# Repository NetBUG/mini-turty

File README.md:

# mini-turty

ROS package for the Mini-Turty robot.

Original product website: https://www.rhoeby.com/product/mini-turty
    
The Mini-Turty Robot from Rhoeby Dynamics represents a new level of value and functionality in a ROS navigation-capable robot. Designed with the lowest cost and complete user serviceability in mind, this robot is providing greatly improved access to advanced robotics navigation and much more!

## Hardware
The repository contains a [sample platform](mini_turty3/hw/lasercut) designed to be made with laser cutting. 
The base is cut out of 3mm birch plywood with principal strength direction oriented transversely (i.e. robot does not bend between the wheels).
Any other elements are cut out of 3 or 4mm acrylic sheet of any color. Motor holders are not optimal and will be improved soon to provide active suspension.
Unfortunately, the front navigation module (can be seen on sheets as a rectangle of 120x85 mm) was made long ago and design was lost. It contains:
 - Raspberry Pi 3 with heatsink, mounted on 4xM2 screws on the bottom sheet;
 - Neato xv11 lidar, mounted on upper sheet (which is elevated with 30mm M3 screws and pipe-like stands)
 - Raspberry Pi 3 extension made on a prototyping board with PLS connectors, providing connections to
  * lidar through on-board UART (serial kernel logging was disabled)
  * lidar motor power through a low-power SOT23 MOSFET
  * stepper driver outputs
  * I2C connector for  sensors (used for IMU)
  * 4xGPIO pins

The following external components have been used and fit on the base:
 - [18650-sized battery holder](https://www.thingiverse.com/thing:456900)
 - [LV8729 drivers](https://www.aliexpress.com/item/32808950520.html)
 - 2xNEMA17 stepper motors with Makeblocks wheels and wheel hubs
 - A [ball stand](https://pandao.ru/product/233c3d45-5e80-4f82-84e4-e2d594d67a44)

The following components have been fit on the upper board
 - A stepdown module using XL6009 chip
 - An [IMU](https://amperka.ru/product/troyka-imu-10-dof)
 - An IR receiver
 - [Power controller board](mini_turty3/hw/controller)

Drawings use the following coloring convention:
 - black means the lines that have to be cut
 - red means lines denoting mounted parts dimensions and should be omitted when cutting (originally it was used as pale dashed line)
 - yellow originally denoted contours filled with yellow and was used in engraving mode to provide submerged areas to hide PCBs or screen frame

## Things You Can Do With Your Mini-Turty Robot

There are many things you can do with your Mini-Turty robot, including:

- Basics: ROS learning
- Teleop: robot remote control
- Map Building: make maps of your home or office for the robot to use
- Navigation: the robot moves autonomously around your home or office
- Tele-Viewing: see what your robot sees, even from another room*
- Frontier Exploration: the robot autonomously explores unknown terrain*
- Computer Vision: Mini-Turty recognizes objects in its environment*

*Coming soon, to a robot near you!

Available in kit form*, or fully assembled and ready to go. Either way, Mini-Turty provides endless hours of educational fun and represents the ideal platform for learning the Robot Operating System.

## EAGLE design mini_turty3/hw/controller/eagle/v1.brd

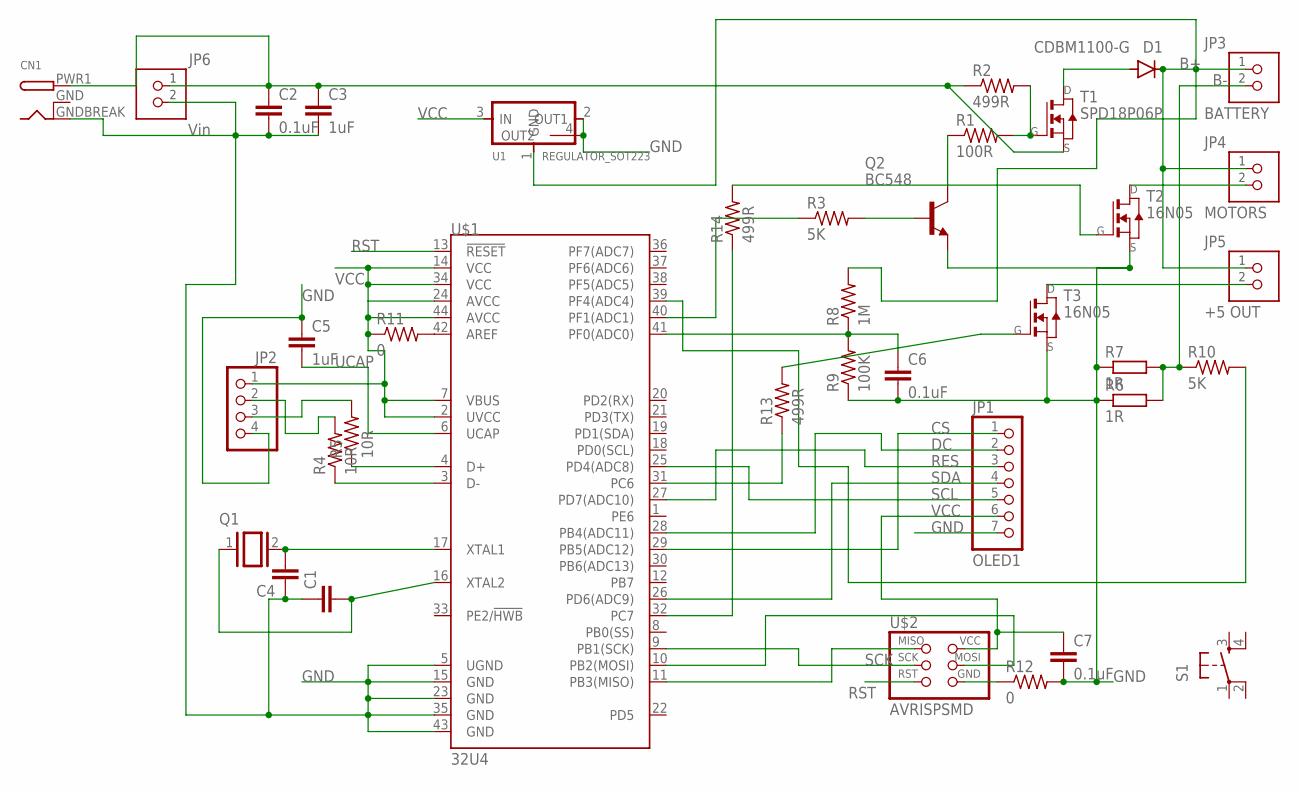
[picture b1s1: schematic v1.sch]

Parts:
C1, C4: C-EUC1206; C1206
C2, C6, C7: 0.1uF; C1206
C3, C5: 1uF; C1206
CN1: DCBARRELSMT; DCJACK_2MM_SMT
D1: CDBM1100-G; MINI-SMA
JP1: OLED1; 1X07
JP2: PINHD-1X4; 1X04
JP3: BATTERY; ED555DS-2DS
JP4: MOTORS; ED555DS-2DS
JP5: +5 OUT; ED555DS-2DS
JP6: Vin; ED555DS-2DS
Q1: XTAL/S; QS
Q2: BC548; TO92-EBC
R1: 100R; M1206
R2, R13, R14: 499R; M1206
R3, R10: 5K; M1206
R4, R5: 10R; M1206
R6, R7: 1R; R6332W
R8: 1M; M1206
R9: 100K; M1206
R11, R12: 0; M1206
S1: 6MM_SWITCH6MM_SWITCH; 6MM_SWITCH
T1: SPD18P06P; TO252
T2, T3: 16N05; TO252
U1: REGULATOR_SOT223; SOT223
U$1: 32U4; TQFP44
U$2: AVRISPSMD; 2X03SMD

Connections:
B+: D1.KATHODE, JP3.1, JP4.1, JP5.1, R8.2, U1.1 (GND)
B-: JP3.2, R6.2, R7.2, R10.1
CS: JP1.1, U$1.29 (PB5(ADC12))
DC: JP1.2, U$1.28 (PB4(ADC11))
GND: C1.1, C2.2, C3.2, C4.1, C5.1, C6.2, C7.2, CN1.GNDBREAK (GND), JP1.7, JP2.4, JP6.2, Q2.E, R6.1, R7.1, R9.1, R12.2, T2.2 (S), T3.2 (S), U1.2 (OUT1), U1.4 (OUT2), U$1.5 (UGND), U$1.15 (GND), U$1.23 (GND), U$1.35 (GND), U$1.43 (GND)
GNDBREAK: CN1.GND (GNDBREAK)
MISO: U$1.11 (PB3(MISO)), U$2.1 (MISO)
MOSI: U$1.10 (PB2(MOSI)), U$2.4 (MOSI)
unnamed: C4.2, Q1.2, U$1.17 (XTAL1)
unnamed: R11.2, U$1.42 (AREF)
unnamed: R3.1, U$1.40 (PF1(ADC1))
unnamed: R12.1, U$2.6 (GND)
unnamed: C1.2, Q1.1, U$1.16 (XTAL2)
unnamed: JP5.2, T3.3 (D)
unnamed: JP4.2, T2.3 (D)
unnamed: R14.1, U$1.32 (PC7)
unnamed: D1.ANODE, T1.3 (D)
unnamed: R1.2, R2.2, T1.1 (G)
unnamed: Q2.C, R1.1
unnamed: Q2.B, R3.2
unnamed: R13.1, U$1.31 (PC6)
unnamed: C6.1, R8.1, R9.2, U$1.41 (PF0(ADC0))
unnamed: R10.2, U$1.39 (PF4(ADC4))
unnamed: JP2.3, R5.2
unnamed: R5.1, U$1.4 (D+)
unnamed: R4.1, U$1.3 (D-)
unnamed: JP2.2, R4.2
unnamed: R14.2, T2.1 (G)
unnamed: R13.2, T3.1 (G)
RES: JP1.3, U$1.27 (PD7(ADC10))
RST: U$1.13 (!RESET), U$2.5 (RST)
SCK: U$1.9 (PB1(SCK)), U$2.3 (SCK)
SCL: JP1.5, U$1.25 (PD4(ADC8))
SDA: JP1.4, U$1.26 (PD6(ADC9))
UCAP: C5.2, U$1.6 (UCAP)
VCC: C7.1, JP1.6, JP2.1, R11.1, U1.3 (IN), U$1.2 (UVCC), U$1.7 (VBUS), U$1.14 (VCC), U$1.24 (AVCC), U$1.34 (VCC), U$1.44 (AVCC), U$2.2 (VCC)
VIN: C2.1, C3.1, CN1.PWR1 (PWR), JP6.1, R2.1, T1.2 (S)

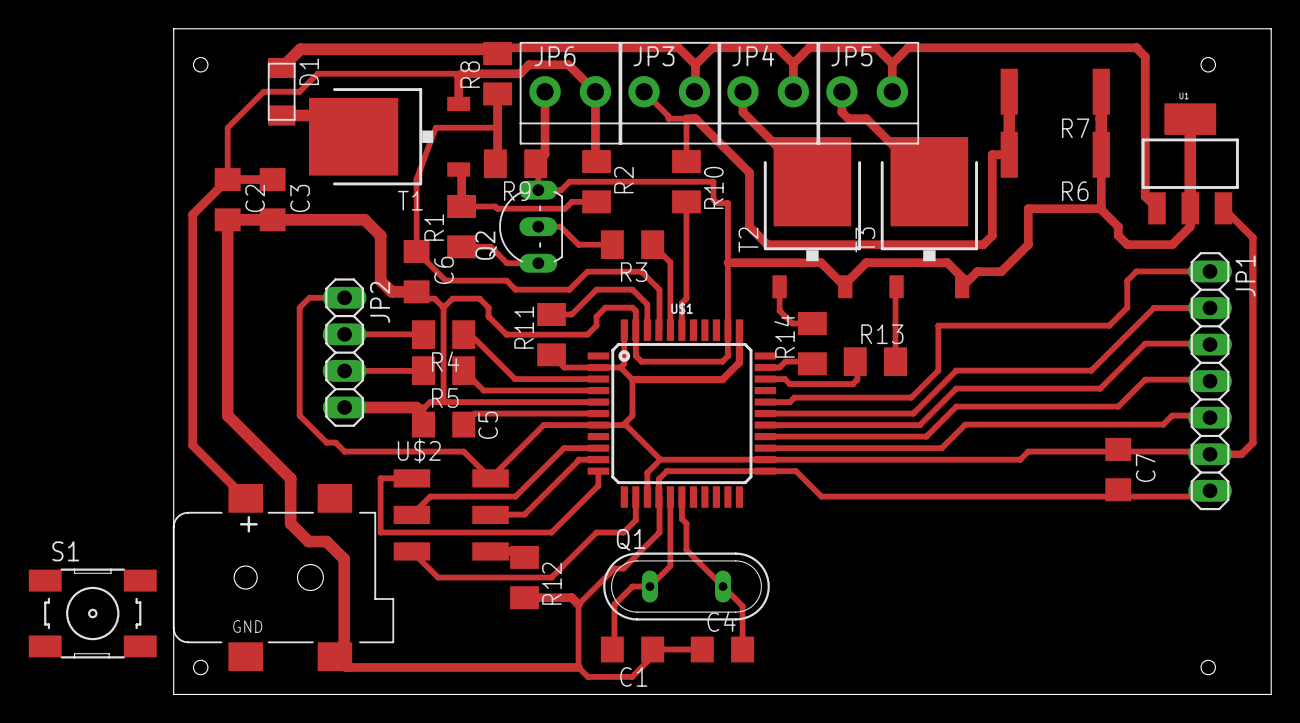
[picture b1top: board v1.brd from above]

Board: 2 copper layers, 76.2 x 46.2 mm, 38 parts (0 on the bottom side), 36 nets.

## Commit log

2019-06-02 Change pin assignment for Fabbot
2019-06-02 Add a bare bone launch to check operations
2019-06-04 Fix motional speed and some bindings
2019-06-08 Improved manual motion
2019-12-05 Added sources
2019-12-05 Modified README
2019-12-05 Added drawing coloring convention

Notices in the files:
parts and their libraries:
SparkFun-IC-Microcontroller: Licensing: Creative Commons ShareAlike 4.0 International - https://creativecommons.org/licenses/by-sa/4.0
